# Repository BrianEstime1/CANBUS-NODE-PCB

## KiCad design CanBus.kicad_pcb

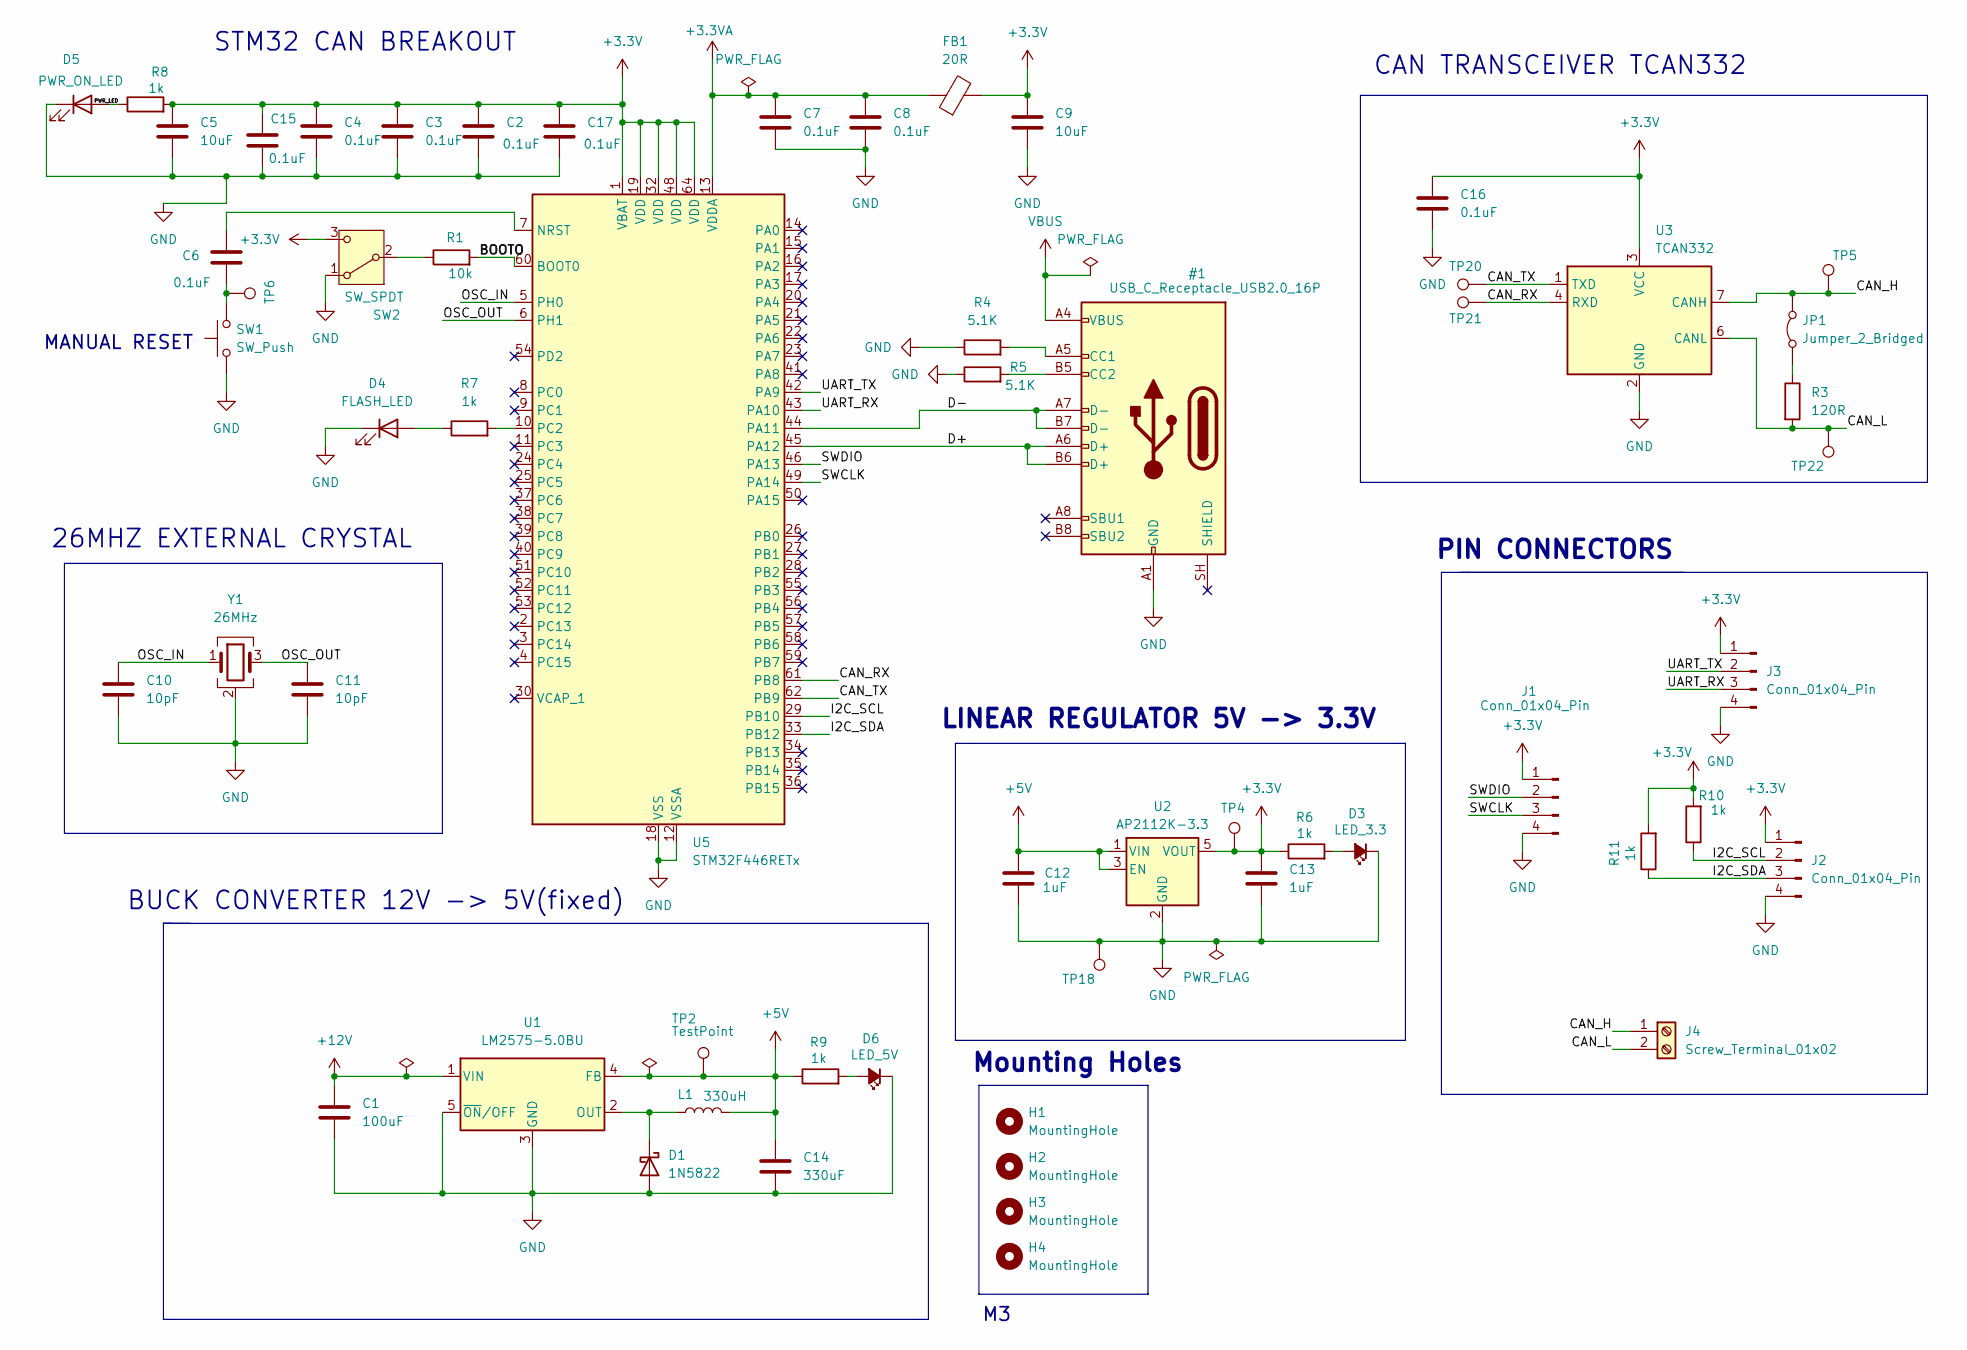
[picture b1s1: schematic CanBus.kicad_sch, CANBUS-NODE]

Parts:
C1: 100uF; C_Elec_8x10.2; LCSC C176672
C2, C3, C4, C6, C7, C8, C15, C16, C17: 0.1uF; C_0603_1608Metric
C5, C9: 10uF; C_0603_1608Metric
C10, C11: 10pF; C_0603_1608Metric
C12, C13: 1uF; C_0603_1608Metric
C14: 330uF; C_Elec_10x10.2; LCSC C176675
D1: 1N5822; D_DO-201AD_P15.24mm_Horizontal; LCSC C2476
D3: LED_3.3; LED_0603_1608Metric; LCSC C84256
D4: FLASH_LED; LED_0603_1608Metric; LCSC C84256
D5: PWR_ON_LED; LED_0603_1608Metric; LCSC C84256
D6: LED_5V; LED_0603_1608Metric; LCSC C84256
FB1: 20R; L_0603_1608Metric; LCSC C394467
H1, H2, H3, H4: MountingHole; MountingHole_3.2mm_M3
J1, J2, J3: Conn_01x04_Pin; PinHeader_1x04_P2.54mm_Vertical
J4: Screw_Terminal_01x02; TerminalBlock_Phoenix_MKDS-1,5-2-5.08_1x02_P5.08mm_Horizont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
JP1: Jumper_2_Bridged; SolderJumper-2_P1.3mm_Bridged_Pad1.0x1.5mm
L1: 330uH; L_12x12mm_H6mm; LCSC C2453076
R1: 10k; R_0603_1608Metric
R3: 120R; R_0603_1608Metric
R4, R5: 5.1K; R_0603_1608Metric
R6, R7, R8, R9, R10, R11: 1k; R_0603_1608Metric
SW1: SW_Push; SW_SPST_TL3305B
SW2: SW_SPDT; SW_SPDT_PCM12
TP2, TP4, TP6, TP18, TP20, TP21: TestPoint; TestPoint_Pad_1.0x1.0mm
TP5, TP22: TestPoint; TestPoint_Loop_D1.80mm_Drill1.0mm_Beaded
U1: LM2575-5.0BU; TO-263-5_TabPin3
U2: AP2112K-3.3; SOT-23-5; LCSC C51118
U3: TCAN332; TSOT-23-8; LCSC C544741
U5: STM32F446RETx; LQFP-64_10x10mm_P0.5mm; LCSC C69336
Y1: 26MHz; Crystal_SMD_Abracon_ABM8G-4Pin_3.2x2.5mm; LCSC C7065088

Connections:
+3.3V: C2.1, C3.1, C4.1, C5.1, C9.1, C13.1, C15.1, C16.1, C17.1, FB1.2, J1.1, J2.1, J3.1, R6.1, R8.2, R10.2, R11.2, SW2.3 (C), TP4.1 (1_1), U2.5 (VOUT), U3.3 (VCC), U5.1 (VBAT), U5.19 (VDD), U5.32 (VDD), U5.48 (VDD), U5.64 (VDD)
+3.3VA: C7.1, C8.1, FB1.1, U5.13 (VDDA)
+5V: C12.1, C14.1, L1.2, R9.1, TP2.1 (1_1), U1.4 (FB), U2.1 (VIN), U2.3 (EN)
+12V: C1.1, U1.1 (VIN)
/BOOTO: R1.2, U5.60 (BOOT0)
/CAN_H: J4.1, JP1.2 (B), TP5.1 (1_1), U3.7 (CANH)
/CAN_L: J4.2, R3.2, TP22.1 (1_1), U3.6 (CANL)
/CAN_RX: TP21.1 (1_1), U3.4 (RXD), U5.61 (PB8)
/CAN_TX: TP20.1 (1_1), U3.1 (TXD), U5.62 (PB9)
/I2C_SCL: J2.2, R10.1, U5.29 (PB10)
/I2C_SDA: J2.3, R11.1, U5.33 (PB12)
/OSC_IN: C10.1, U5.5 (PH0), Y1.1
/OSC_OUT: C11.1, U5.6 (PH1), Y1.3
/PWR_LED: D5.2 (A), R8.1
/SWCLK: J1.3, U5.49 (PA14)
/SWDIO: J1.2, U5.46 (PA13)
/UART_RX: J3.3, U5.43 (PA10)
/UART_TX: J3.2, U5.42 (PA9)
unnamed: C6.2, SW1.2, TP6.1 (1_1)
unnamed: D1.1 (K), L1.1, U1.2 (OUT)
unnamed: D3.2 (A), R6.2
unnamed: D4.2 (A), R7.1
unnamed: D6.2 (A), R9.2
unnamed: JP1.1 (A), R3.1
unnamed: R1.1, SW2.2 (B)
unnamed: C6.1, U5.7 (NRST)
unnamed: R7.2, U5.10 (PC2)

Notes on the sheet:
Mounting Holes
MANUAL RESET
26MHZ EXTERNAL CRYSTAL
STM32 CAN BREAKOUT
LINEAR REGULATOR 5V -> 3.3V
CAN TRANSCEIVER TCAN332
BUCK CONVERTER 12V -> 5V(fixed)
PIN CONNECTORS

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
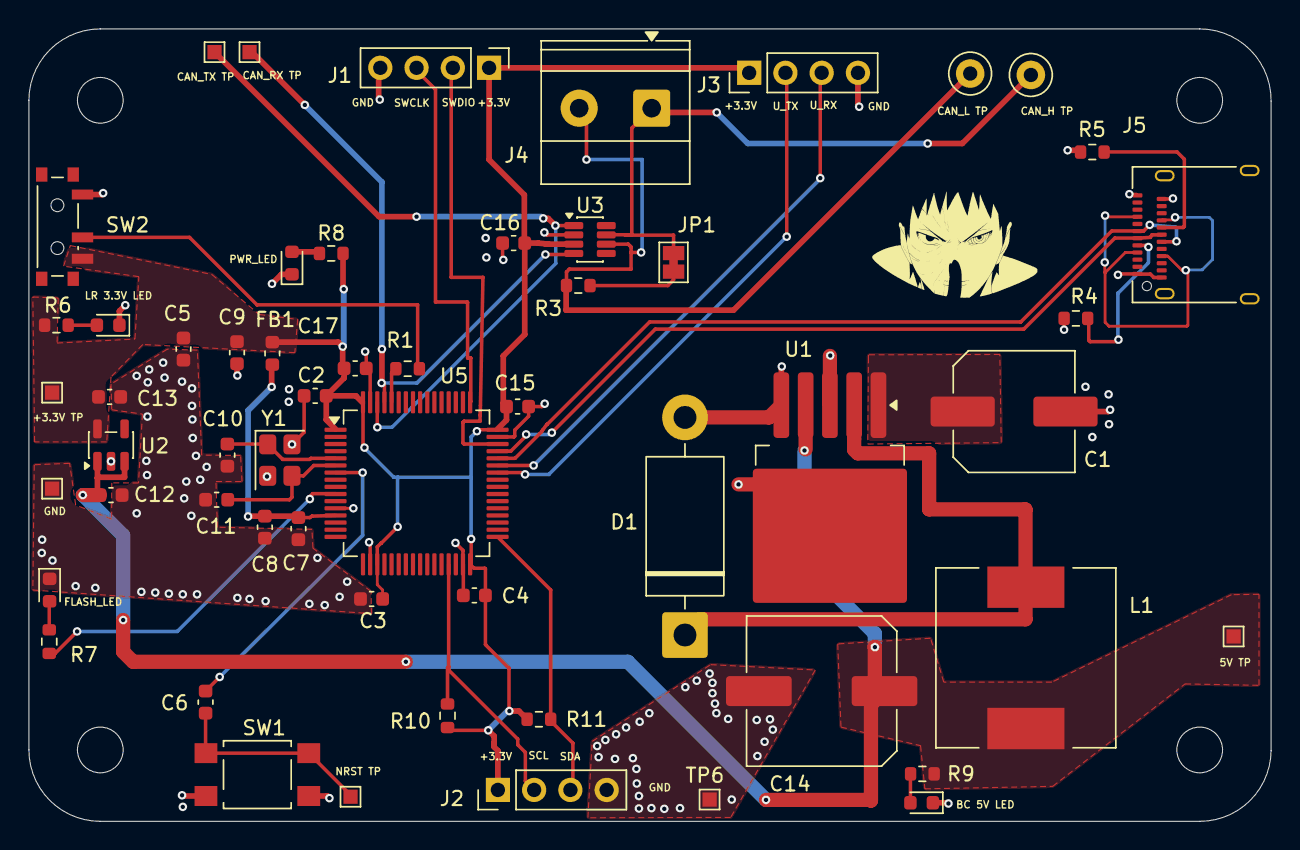
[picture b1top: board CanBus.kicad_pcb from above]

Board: 4 copper layers, 87.0 x 55.5 mm, 60 parts (0 on the bottom side), 33 nets.

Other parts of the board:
J5: USB_C_Receptacle_USB2.0_16P; USB_C_Receptacle_Amphenol_12401610E4-2A
TP6#2: TestPoint; TestPoint_Pad_1.0x1.0mm

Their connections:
VBUS: J5.A4 (VBUS), J5.A9 (VBUS), J5.B4 (VBUS), J5.B9 (VBUS)

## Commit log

2026-06-30 Add CAN Bus Node PCB KiCad project files and Gerber outputs
    - KiCad 10.0 project files (kicad_pcb, kicad_sch, kicad_pro, kicad_prl)
    - Full Gerber fabrication set: F.Cu, B.Cu, In1.Cu, In2.Cu, masks, silkscreen, edge cuts
    - Drill files (PTH + NPTH) and component placement CSV
    - 4-layer STM32F446RET6 CAN bus breakout board with TCAN332 transceiver
2026-06-30 Update README with images for CANBUS-NODE-PCB
    Added images to README for better visualization.
2026-06-30 Add additional images to README
2026-06-30 Update images in README.md
    Removed duplicate images and added a new image.
2026-06-30 Update README with additional images
    Added multiple images to the README for better visualization.
2026-06-30 Update README to remove unnecessary images
    Removed two images from the README.
